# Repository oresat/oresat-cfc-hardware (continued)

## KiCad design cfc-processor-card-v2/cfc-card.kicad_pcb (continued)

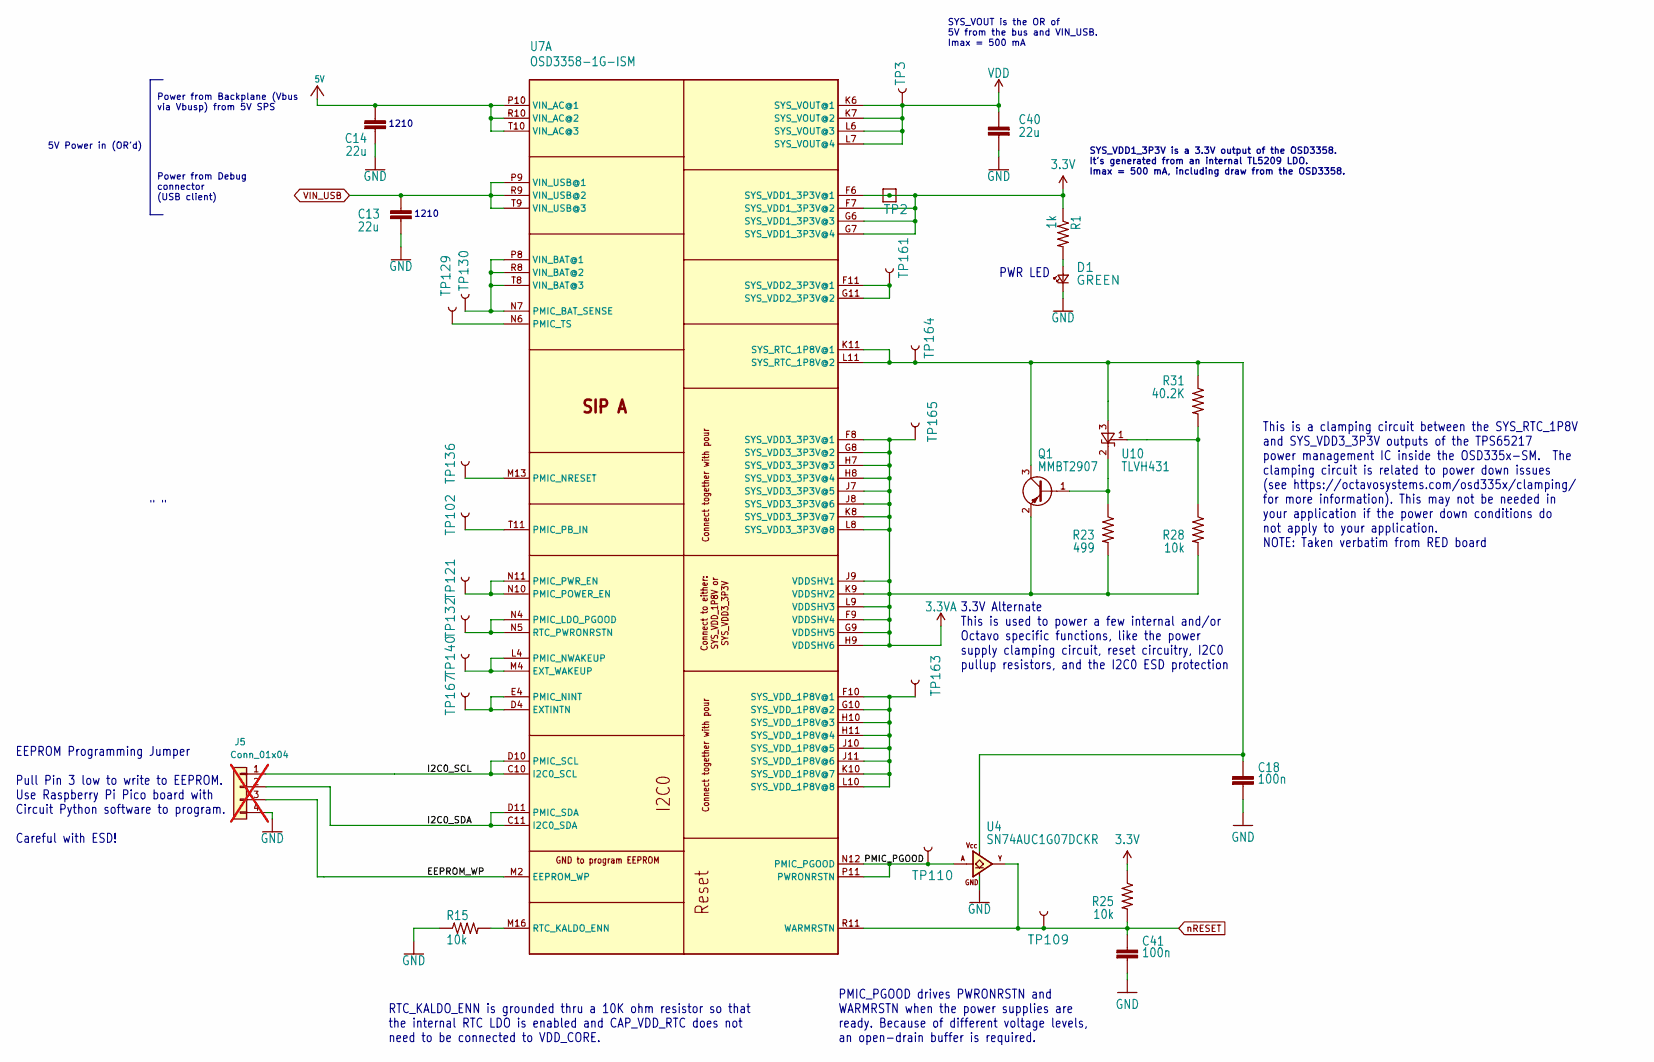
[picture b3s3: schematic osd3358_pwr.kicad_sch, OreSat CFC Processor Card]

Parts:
C13, C14, C40: 22u; C_1210_3225Metric; MPN GCM32EC71E226KE36K
C18, C41: 100n; 0603-C-NOSILK; MPN TMK107BJ104KAHT
D1: GREEN; LED_0603_1608Metric; MPN 150060GS75000
J5: Conn_01x04; PinHeader_1x04_P2.54mm_Vertical; not fitted
Q1: MMBT2907; SOT-23; MPN PMBT2907A,235
R1: 1k; 0603-C-NOSILK; MPN RMCF0603FT1K00
R15, R25, R28: 10k; 0603-C-NOSILK; MPN RMCF0603FT10K0
R23: 499; 0603-C-NOSILK; MPN RMCF0603FT499R
R31: 40.2K; 0603-C-NOSILK; MPN RMCF0603FT40K2
TP2: TEST-POINT; 2MM-TEST-POINT
TP3, TP102, TP109, TP110, TP121, TP129, TP130, TP132, TP136, TP140, TP161, TP163, TP164, TP165, TP167: TEST-POINT3X4; PAD.03X.04
U4: SN74AUC1G07DCKR; SOT-353_SC-70-5; MPN SN74AUC1G07DCKR
U7: OSD3358-1G-ISM; U-Octavo-OSD335X-BGA-256; MPN OSD3358-1G-ISM
U10: TLVH431; SOT-23; MPN TLVH431BCDBZT

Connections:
3.3V: R1.1, R25.1, TP2.1, U7.F6 (SYS_VDD1_3P3V@1), U7.F7 (SYS_VDD1_3P3V@2), U7.G6 (SYS_VDD1_3P3V@3), U7.G7 (SYS_VDD1_3P3V@4); also elsewhere on the board
3.3VA: Q1.2 (E), R23.2, R28.2, TP165.P$1 (1), U7.F8 (SYS_VDD3_3P3V@1), U7.F9 (VDDSHV4), U7.G8 (SYS_VDD3_3P3V@2), U7.G9 (VDDSHV5), U7.H7 (SYS_VDD3_3P3V@3), U7.H8 (SYS_VDD3_3P3V@4), U7.H9 (VDDSHV6), U7.J7 (SYS_VDD3_3P3V@5), U7.J8 (SYS_VDD3_3P3V@6), U7.J9 (VDDSHV1), U7.K8 (SYS_VDD3_3P3V@7), U7.K9 (VDDSHV2), U7.L8 (SYS_VDD3_3P3V@8), U7.L9 (VDDSHV3)
5V: C14.1, U7.P10 (VIN_AC@1), U7.R10 (VIN_AC@2), U7.T10 (VIN_AC@3); also elsewhere on the board
/OSD3358: SIP A (PWR)/EEPROM_WP: J5.3, U7.M2 (EEPROM_WP)
/OSD3358: SIP A (PWR)/I2C0_SCL: J5.1, U7.C10 (I2C0_SCL), U7.D10 (PMIC_SCL)
/OSD3358: SIP A (PWR)/I2C0_SDA: J5.2, U7.C11 (I2C0_SDA), U7.D11 (PMIC_SDA)
/OSD3358: SIP A (PWR)/PMIC_PGOOD: TP110.P$1 (1), U4.2 (A), U7.N12 (PMIC_PGOOD), U7.P11 (PWRONRSTN)
GND: C13.2, C14.2, C18.2, C40.2, C41.2, D1.1 (K), J5.4, R15.1, U4.3 (GND); also elsewhere on the board
unnamed: D1.2 (A), R1.2
unnamed: Q1.1 (B), R23.1, U10.2 (K)
unnamed: C18.1, Q1.3 (C), R31.1, TP164.P$1 (1), U4.5 (VCC), U7.K11 (SYS_RTC_1P8V@1), U7.L11 (SYS_RTC_1P8V@2), U10.3 (A)
unnamed: TP102.P$1 (1), U7.T11 (PMIC_PB_IN)
unnamed: TP121.P$1 (1), U7.N10 (PMIC_POWER_EN), U7.N11 (PMIC_PWR_EN)
unnamed: TP129.P$1 (1), U7.N6 (PMIC_TS)
unnamed: TP130.P$1 (1), U7.N7 (PMIC_BAT_SENSE), U7.P8 (VIN_BAT@1), U7.R8 (VIN_BAT@2), U7.T8 (VIN_BAT@3)
unnamed: TP132.P$1 (1), U7.N4 (PMIC_LDO_PGOOD), U7.N5 (RTC_PWRONRSTN)
unnamed: TP136.P$1 (1), U7.M13 (PMIC_NRESET)
unnamed: TP140.P$1 (1), U7.L4 (PMIC_NWAKEUP), U7.M4 (EXT_WAKEUP)
unnamed: TP161.P$1 (1), U7.F11 (SYS_VDD2_3P3V@1), U7.G11 (SYS_VDD2_3P3V@2)
unnamed: TP163.P$1 (1), U7.F10 (SYS_VDD_1P8V@1), U7.G10 (SYS_VDD_1P8V@2), U7.H10 (SYS_VDD_1P8V@3), U7.H11 (SYS_VDD_1P8V@4), U7.J10 (SYS_VDD_1P8V@5), U7.J11 (SYS_VDD_1P8V@6), U7.K10 (SYS_VDD_1P8V@7), U7.L10 (SYS_VDD_1P8V@8)
unnamed: TP167.P$1 (1), U7.D4 (EXTINTN), U7.E4 (PMIC_NINT)
unnamed: R15.2, U7.M16 (RTC_KALDO_ENN)
unnamed: R28.1, R31.2, U10.1 (REF)
VDD: C40.1, TP3.P$1 (1), U7.K6 (SYS_VOUT@1), U7.K7 (SYS_VOUT@2), U7.L6 (SYS_VOUT@3), U7.L7 (SYS_VOUT@4); also elsewhere on the board
VIN_USB: C13.1, U7.P9 (VIN_USB@1), U7.R9 (VIN_USB@2), U7.T9 (VIN_USB@3); also elsewhere on the board
nRESET: C41.1, R25.2, TP109.P$1 (1), U4.4 (Y), U7.R11 (WARMRSTN); also elsewhere on the board

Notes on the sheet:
SYS_VDD1_3P3V is a 3.3V output of the OSD3358. It's generated from an internal TL5209 LDO. Imax = 500 mA, including draw from the OSD3358.
PMIC_PGOOD drives PWRONRSTN and WARMRSTN when the power supplies are ready. Because of different voltage levels, an open-drain buffer is required.
" "
5V Power in (OR'd)
RTC_KALDO_ENN is grounded thru a 10K ohm resistor so that the internal RTC LDO is enabled and CAP_VDD_RTC does not need to be connected to VDD_CORE.
This is a clamping circuit between the SYS_RTC_1P8V and SYS_VDD3_3P3V outputs of the TPS65217 power management IC inside the OSD335x-SM. The clamping circuit is related to power down issues (see https://octavosystems.com/osd335x/clamping/ for more information). This may not be needed in your applic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
PWR LED
1210
EEPROM Programming Jumper Pull Pin 3 low to write to EEPROM. Use Raspberry Pi Pico board with Circuit Python software to program. Careful with ESD!
SYS_VOUT is the OR of 5V from the bus and VIN_USB. Imax = 500 mA
Power from Debug connector (USB client)
3.3V Alternate This is used to power a few internal and/or Octavo specific functions, like the power supply clamping circuit, reset circuitry, I2C0 pullup resistors, and the I2C0 ESD protection
Power from Backplane (Vbus via Vbusp) from 5V SPS

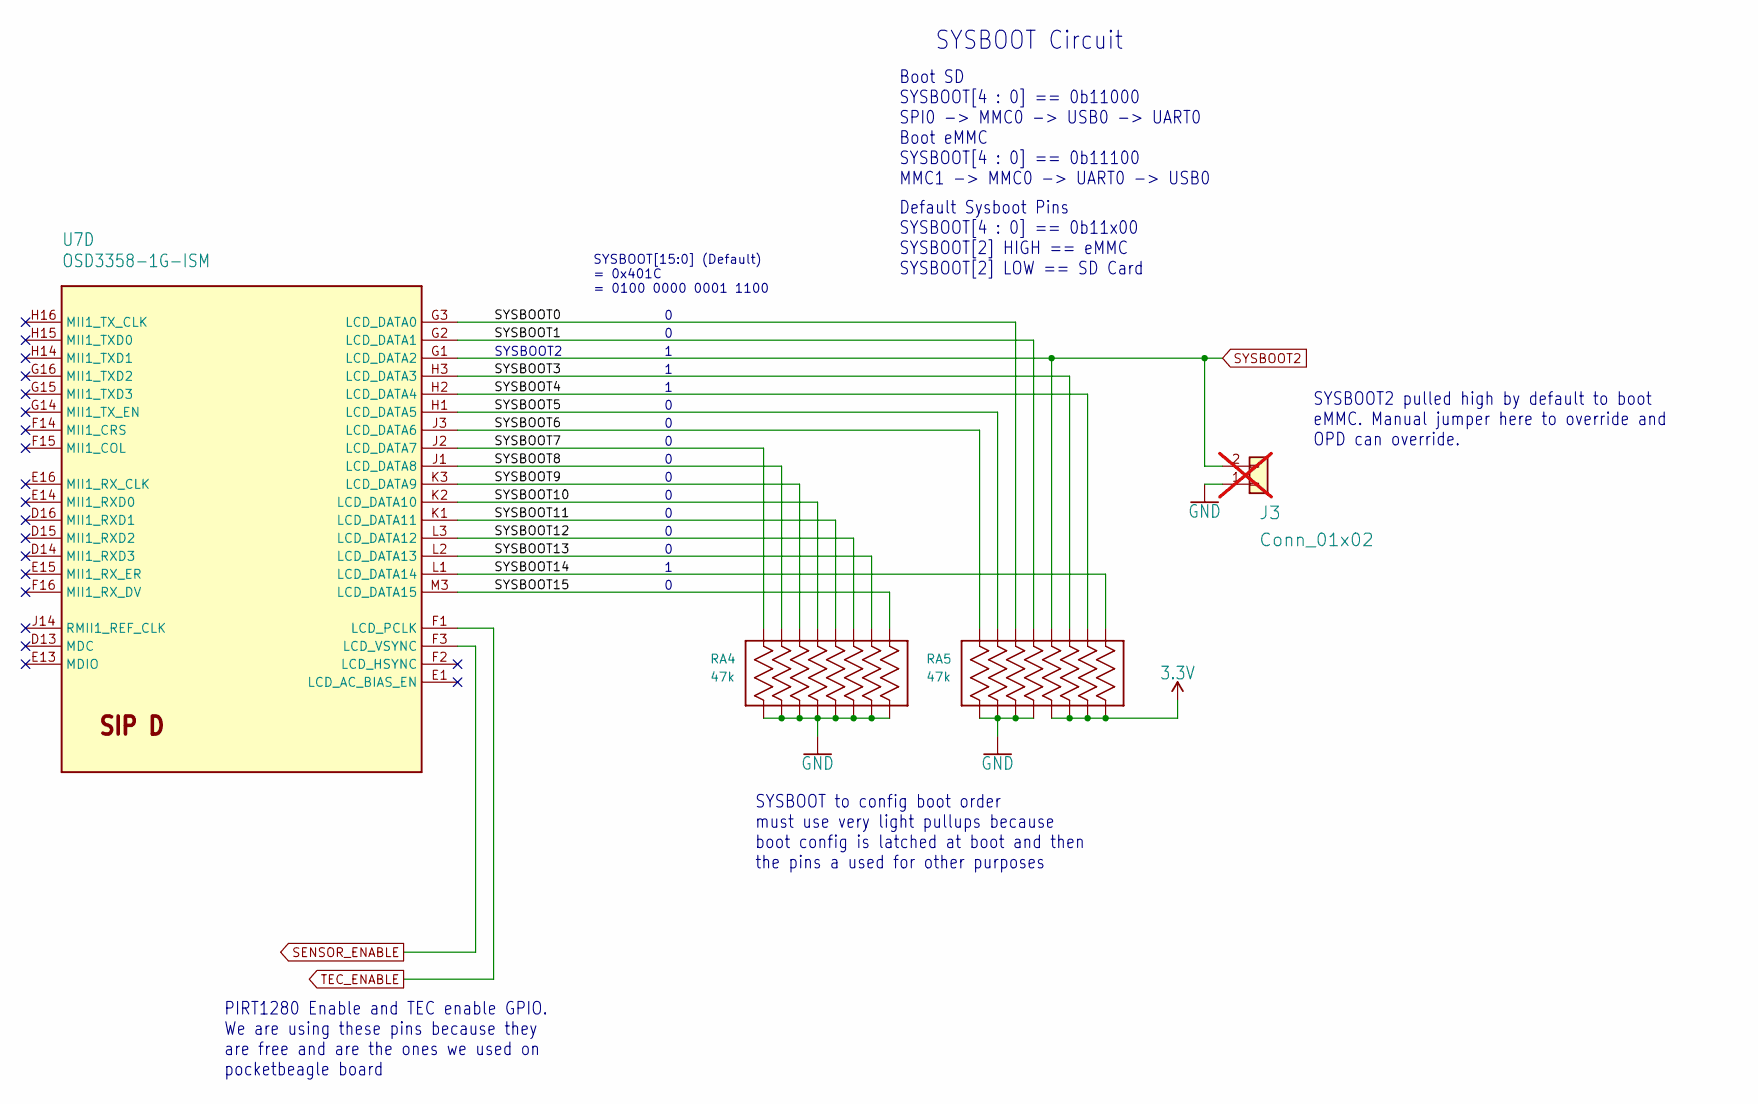
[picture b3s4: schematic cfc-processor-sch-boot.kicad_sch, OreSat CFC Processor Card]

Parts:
J3: Conn_01x02; PinHeader_1x02_P2.54mm_Vertical; not fitted
RA4, RA5: 47k; RES_EXB2HV; MPN EXB-2HV473JV
U7: OSD3358-1G-ISM; U-Octavo-OSD335X-BGA-256; MPN OSD3358-1G-ISM

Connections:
3.3V: RA5.5, RA5.6, RA5.7, RA5.8; also elsewhere on the board
/OSD3358: SIP D (BOOT)/SYSBOOT0: RA5.14, U7.G3 (LCD_DATA0)
/OSD3358: SIP D (BOOT)/SYSBOOT1: RA5.13, U7.G2 (LCD_DATA1)
/OSD3358: SIP D (BOOT)/SYSBOOT3: RA5.11, U7.H3 (LCD_DATA3)
/OSD3358: SIP D (BOOT)/SYSBOOT4: RA5.10, U7.H2 (LCD_DATA4)
/OSD3358: SIP D (BOOT)/SYSBOOT5: RA5.15, U7.H1 (LCD_DATA5)
/OSD3358: SIP D (BOOT)/SYSBOOT6: RA5.16, U7.J3 (LCD_DATA6)
/OSD3358: SIP D (BOOT)/SYSBOOT7: RA4.16, U7.J2 (LCD_DATA7)
/OSD3358: SIP D (BOOT)/SYSBOOT8: RA4.15, U7.J1 (LCD_DATA8)
/OSD3358: SIP D (BOOT)/SYSBOOT9: RA4.14, U7.K3 (LCD_DATA9)
/OSD3358: SIP D (BOOT)/SYSBOOT10: RA4.13, U7.K2 (LCD_DATA10)
/OSD3358: SIP D (BOOT)/SYSBOOT11: RA4.12, U7.K1 (LCD_DATA11)
/OSD3358: SIP D (BOOT)/SYSBOOT12: RA4.11, U7.L3 (LCD_DATA12)
/OSD3358: SIP D (BOOT)/SYSBOOT13: RA4.10, U7.L2 (LCD_DATA13)
/OSD3358: SIP D (BOOT)/SYSBOOT14: RA5.9, U7.L1 (LCD_DATA14)
/OSD3358: SIP D (BOOT)/SYSBOOT15: RA4.9, U7.M3 (LCD_DATA15)
GND: J3.1, RA4.1, RA4.2, RA4.3, RA4.4, RA4.5, RA4.6, RA4.7, RA4.8, RA5.1, RA5.2, RA5.3, RA5.4; also elsewhere on the board
SENSOR_ENABLE: U7.F3 (LCD_VSYNC); also elsewhere on the board
SYSBOOT2: J3.2, RA5.12, U7.G1 (LCD_DATA2); also elsewhere on the board
TEC_ENABLE: U7.F1 (LCD_PCLK); also elsewhere on the board

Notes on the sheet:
PIRT1280 Enable and TEC enable GPIO. We are using these pins because they are free and are the ones we used on pocketbeagle board
SYSBOOT Circuit
SYSBOOT[15:0] (Default) = 0x401C = 0100 0000 0001 1100
Boot SD SYSBOOT[4 : 0] == 0b11000 SPI0 -> MMC0 -> USB0 -> UART0 Boot eMMC SYSBOOT[4 : 0] == 0b11100 MMC1 -> MMC0 -> UART0 -> USB0
Default Sysboot Pins SYSBOOT[4 : 0] == 0b11x00 SYSBOOT[2] HIGH == eMMC SYSBOOT[2] LOW == SD Card
SYSBOOT to config boot order must use very light pullups because boot config is latched at boot and then the pins a used for other purposes
SYSBOOT2 pulled high by default to boot eMMC. Manual jumper here to override and OPD can override.
SYSBOOT2

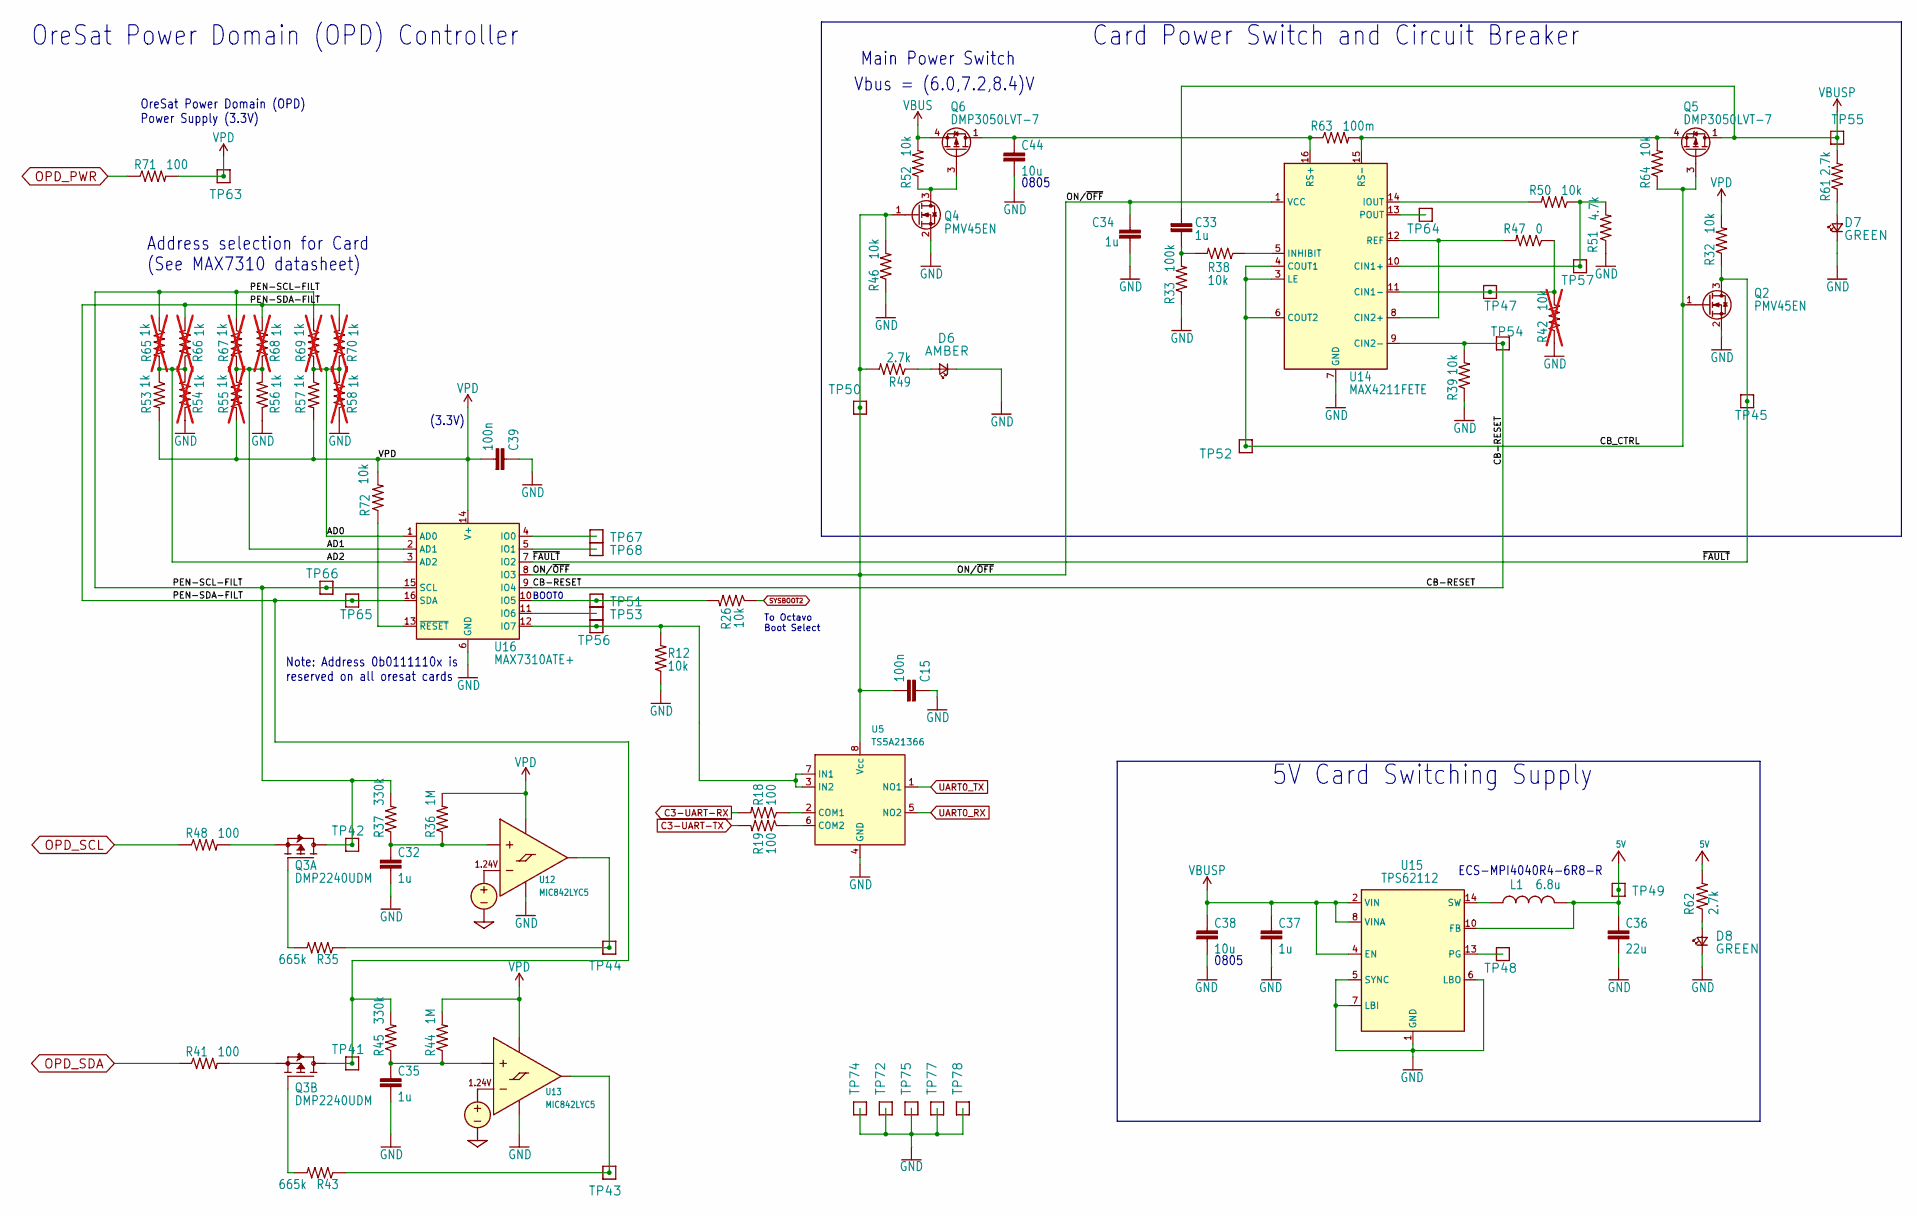
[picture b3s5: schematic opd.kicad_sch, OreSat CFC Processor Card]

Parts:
C15, C39: 100n; 0603-C-NOSILK; MPN TMK107BJ104KAHT
C32, C33, C34, C35, C37: 1u; 0603-C-NOSILK; MPN TMK107BJ105KAHT
C36: 22u; C_1210_3225Metric; MPN GCM32EC71E226KE36K
C38, C44: 10u; 0805-C-NOSILK; MPN GRT21BC71E106KE13L
D6: AMBER; LED_0603_1608Metric; MPN 150060AS75000
D7, D8: GREEN; LED_0603_1608Metric; MPN 150060GS75000
L1: 6.8u; L_ECS-MPI4040; MPN ECS-MPI4040R4-6R8-R
Q2, Q4: PMV45EN; SOT-23-3; MPN PMV45EN2R
Q3: DMP2240UDM; SOT-23-6; MPN DMP2240UDM
Q5, Q6: DMP3050LVT-7; TSOT-23-6; MPN DMP3050LVT-7
R12, R26, R32, R38, R39, R46, R50, R52, R64, R72: 10k; 0603-C-NOSILK; MPN RMCF0603FT10K0
R18, R19, R41, R48, R71: 100; 0603-C-NOSILK; MPN RMCF0603FT100R
R33: 100k; 0603-C-NOSILK; MPN RMCF0603FT100K
R35, R43: 665k; 0603-C-NOSILK; MPN RMCF0603FT665K
R36, R44: 1M; 0603-C-NOSILK; MPN RMCF0603FG1M00
R37, R45: 330k; 0603-C-NOSILK; MPN RMCF0603FT330K
R42: 10k; 0603-C-NOSILK; MPN RC1005F6653CS; not fitted
R47: 0; 0603-C-NOSILK; MPN RMCF0603ZT0R00
R49, R61, R62: 2.7k; 0603-C-NOSILK; MPN RMCF0603FT2K70
R51: 4.7k; 0603-C-NOSILK; MPN RMCF0603FT4K70
R53, R56, R57: 1k; 0603-C-NOSILK; MPN RMCF0603FT1K00
R54, R55, R58, R65, R66, R67, R68, R69, R70: 1k; 0603-C-NOSILK; MPN RC1005F6653CS; not fitted
R63: 100m; 1206-C; MPN CSR1206FTR100
TP41, TP42, TP43, TP44, TP45, TP47, TP48, TP49, TP50, TP51, TP52, TP53, TP54, TP55, TP56, TP57, TP63, TP64, TP65, TP66, TP67, TP68, TP72, TP74, TP75, TP77, TP78: TEST-POINT; 2MM-TEST-POINT
U5: TS5A21366; VSSOP-8_2.3x2mm_P0.5mm; MPN TS5A21366DCUR
U12, U13: MIC842LYC5; SOT-353_SC-70-5; MPN MIC842LYC5-TR
U14: MAX4211FETE; QFN-16-1EP_4x4mm_P0.65mm_EP2.1x2.1mm; MPN MAX4211FETE
U15: TPS62112; Texas_RSA_VQFN-16-1EP_4x4mm_P0.65mm_EP2.7x2.7mm; MPN TPS62112RSAR
U16: MAX7310ATE+; QFN-16-1EP_4x4mm_P0.65mm_EP2.1x2.1mm; MPN MAX7310ATE+

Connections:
5V: C36.1, L1.2, R62.2, TP49.1, U15.10 (FB); also elsewhere on the board
/Power (OPD)/AD0: R57.1, R58.2, R69.2, R70.1, U16.1 (AD0)
/Power (OPD)/AD1: R55.1, R56.2, R67.2, R68.1, U16.2 (AD1)
/Power (OPD)/AD2: R53.1, R54.2, R65.2, R66.1, U16.3 (AD2)
/Power (OPD)/CB-RESET: R39.2, TP54.1, U14.9 (CIN2-), U16.9 (IO4)
/Power (OPD)/CB_CTRL: Q2.1 (G), Q5.3 (G), R64.1, TP52.1, U14.3 (LE), U14.4 (COUT1), U14.6 (COUT2)
/Power (OPD)/ON/~OFF: C15.2, C34.1, Q4.1 (G), R46.2, R49.2, TP50.1, U5.8 (Vcc), U14.1 (VCC), U16.8 (IO3)
/Power (OPD)/PEN-SCL-FILT: Q3.6 (D), R37.2, R65.1, R67.1, R69.1, TP42.1, TP66.1, U16.15 (SCL)
/Power (OPD)/PEN-SDA-FILT: Q3.4 (D), R45.2, R66.2, R68.2, R70.2, TP41.1, TP65.1, U16.16 (SDA)
/Power (OPD)/~FAULT: Q2.3 (D), R32.1, TP45.1, U16.7 (IO2)
C3-UART-RX: R18.2; also elsewhere on the board
C3-UART-TX: R19.2; also elsewhere on the board
GND: C15.1, C32.2, C34.2, C35.2, C36.2, C37.2, C38.2, C39.1, C44.2, D6.1 (K), D7.1 (K), D8.1 (K), Q2.2 (S), Q4.2 (S), R12.1, R33.1, R39.1, R42.1, R46.1, R51.1, R54.1, R56.1, R58.1, TP72.1, TP74.1, TP75.1, TP77.1, TP78.1, U5.4 (GND), U12.2 (GND), U13.2 (GND), U14.7 (GND), U14.17 (GND), U15.1 (GND), U15.5 (SYNC), U15.6 (LBO), U15.7 (LBI), U15.9 (GND), U15.11 (GND), U15.12 (GND), U15.16 (GND), U15.17 (GND), U16.6 (GND), U16.17 (GND); also elsewhere on the board
unnamed: C33.1, R33.2, R38.2
unnamed: D6.2 (A), R49.1
unnamed: D7.2 (A), R61.1
unnamed: D8.2 (A), R62.1
unnamed: L1.1, U15.14 (SW), U15.15 (SW)
unnamed: Q3.1 (G), R35.2
unnamed: Q3.5 (S), R48.2
unnamed: Q3.3 (G), R43.2
unnamed: Q3.2 (S), R41.2
unnamed: Q4.3 (D), Q6.3 (G), R52.1
unnamed: Q5.4 (S), R63.2, R64.2, U14.15 (RS-)
unnamed: R18.1, U5.2 (COM1)
unnamed: R19.1, U5.6 (COM2)
unnamed: C32.1, R36.1, R37.1, U12.1 (INP)
unnamed: R35.1, TP44.1, U12.4 (OUT)
unnamed: C35.1, R44.1, R45.1, U13.1 (INP)
unnamed: R43.1, TP43.1, U13.4 (OUT)
unnamed: R50.1, R51.2, TP57.1, U14.10 (CIN1+)
unnamed: R42.2, R47.1, TP47.1, U14.11 (CIN1-)
unnamed: R47.2, U14.8 (CIN2+), U14.12 (REF)
unnamed: R38.1, U14.5 (INHIBIT)
unnamed: R50.2, U14.14 (IOUT)
unnamed: TP64.1, U14.13 (POUT)
unnamed: C44.1, Q6.1 (D), Q6.2 (D), Q6.5 (D), Q6.6 (D), R63.1, U14.16 (RS+)
unnamed: TP48.1, U15.13 (PG)
unnamed: TP67.1, U16.4 (IO0)
unnamed: TP68.1, U16.5 (IO1)
unnamed: R26.2, TP51.1, U16.10 (IO5)
unnamed: TP53.1, U16.11 (IO6)
unnamed: R12.2, TP56.1, U5.3 (IN2), U5.7 (IN1), U16.12 (IO7)
unnamed: R72.1, U16.13 (~RESET)
OPD_PWR: R71.1; also elsewhere on the board
OPD_SCL: R48.1; also elsewhere on the board
OPD_SDA: R41.1; also elsewhere on the board
SYSBOOT2: R26.1; also elsewhere on the board
UART0_RX: U5.5 (NO2); also elsewhere on the board
UART0_TX: U5.1 (NO1); also elsewhere on the board
VBUS: Q6.4 (S), R52.2; also elsewhere on the board
VBUSP: C33.2, C37.1, C38.1, Q5.1 (D), Q5.2 (D), Q5.5 (D), Q5.6 (D), R61.2, TP55.1, U15.2 (VIN), U15.3 (VIN), U15.4 (EN), U15.8 (VINA)
VPD: C39.2, R32.2, R36.2, R44.2, R53.2, R55.2, R57.2, R71.2, R72.2, TP63.1, U12.5 (VDD), U13.5 (VDD), U16.14 (V+)

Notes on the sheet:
0805
Card Power Switch and Circuit Breaker
BOOT0
Main Power Switch
OreSat Power Domain (OPD) Controller
ECS-MPI4040R4-6R8-R
(3.3V)
OreSat Power Domain (OPD) Power Supply (3.3V)
Address selection for Card (See MAX7310 datasheet)
To Octavo Boot Select
Vbus = (6.0,7.2,8.4)V
5V Card Switching Supply
Note: Address 0b0111110x is reserved on all oresat cards

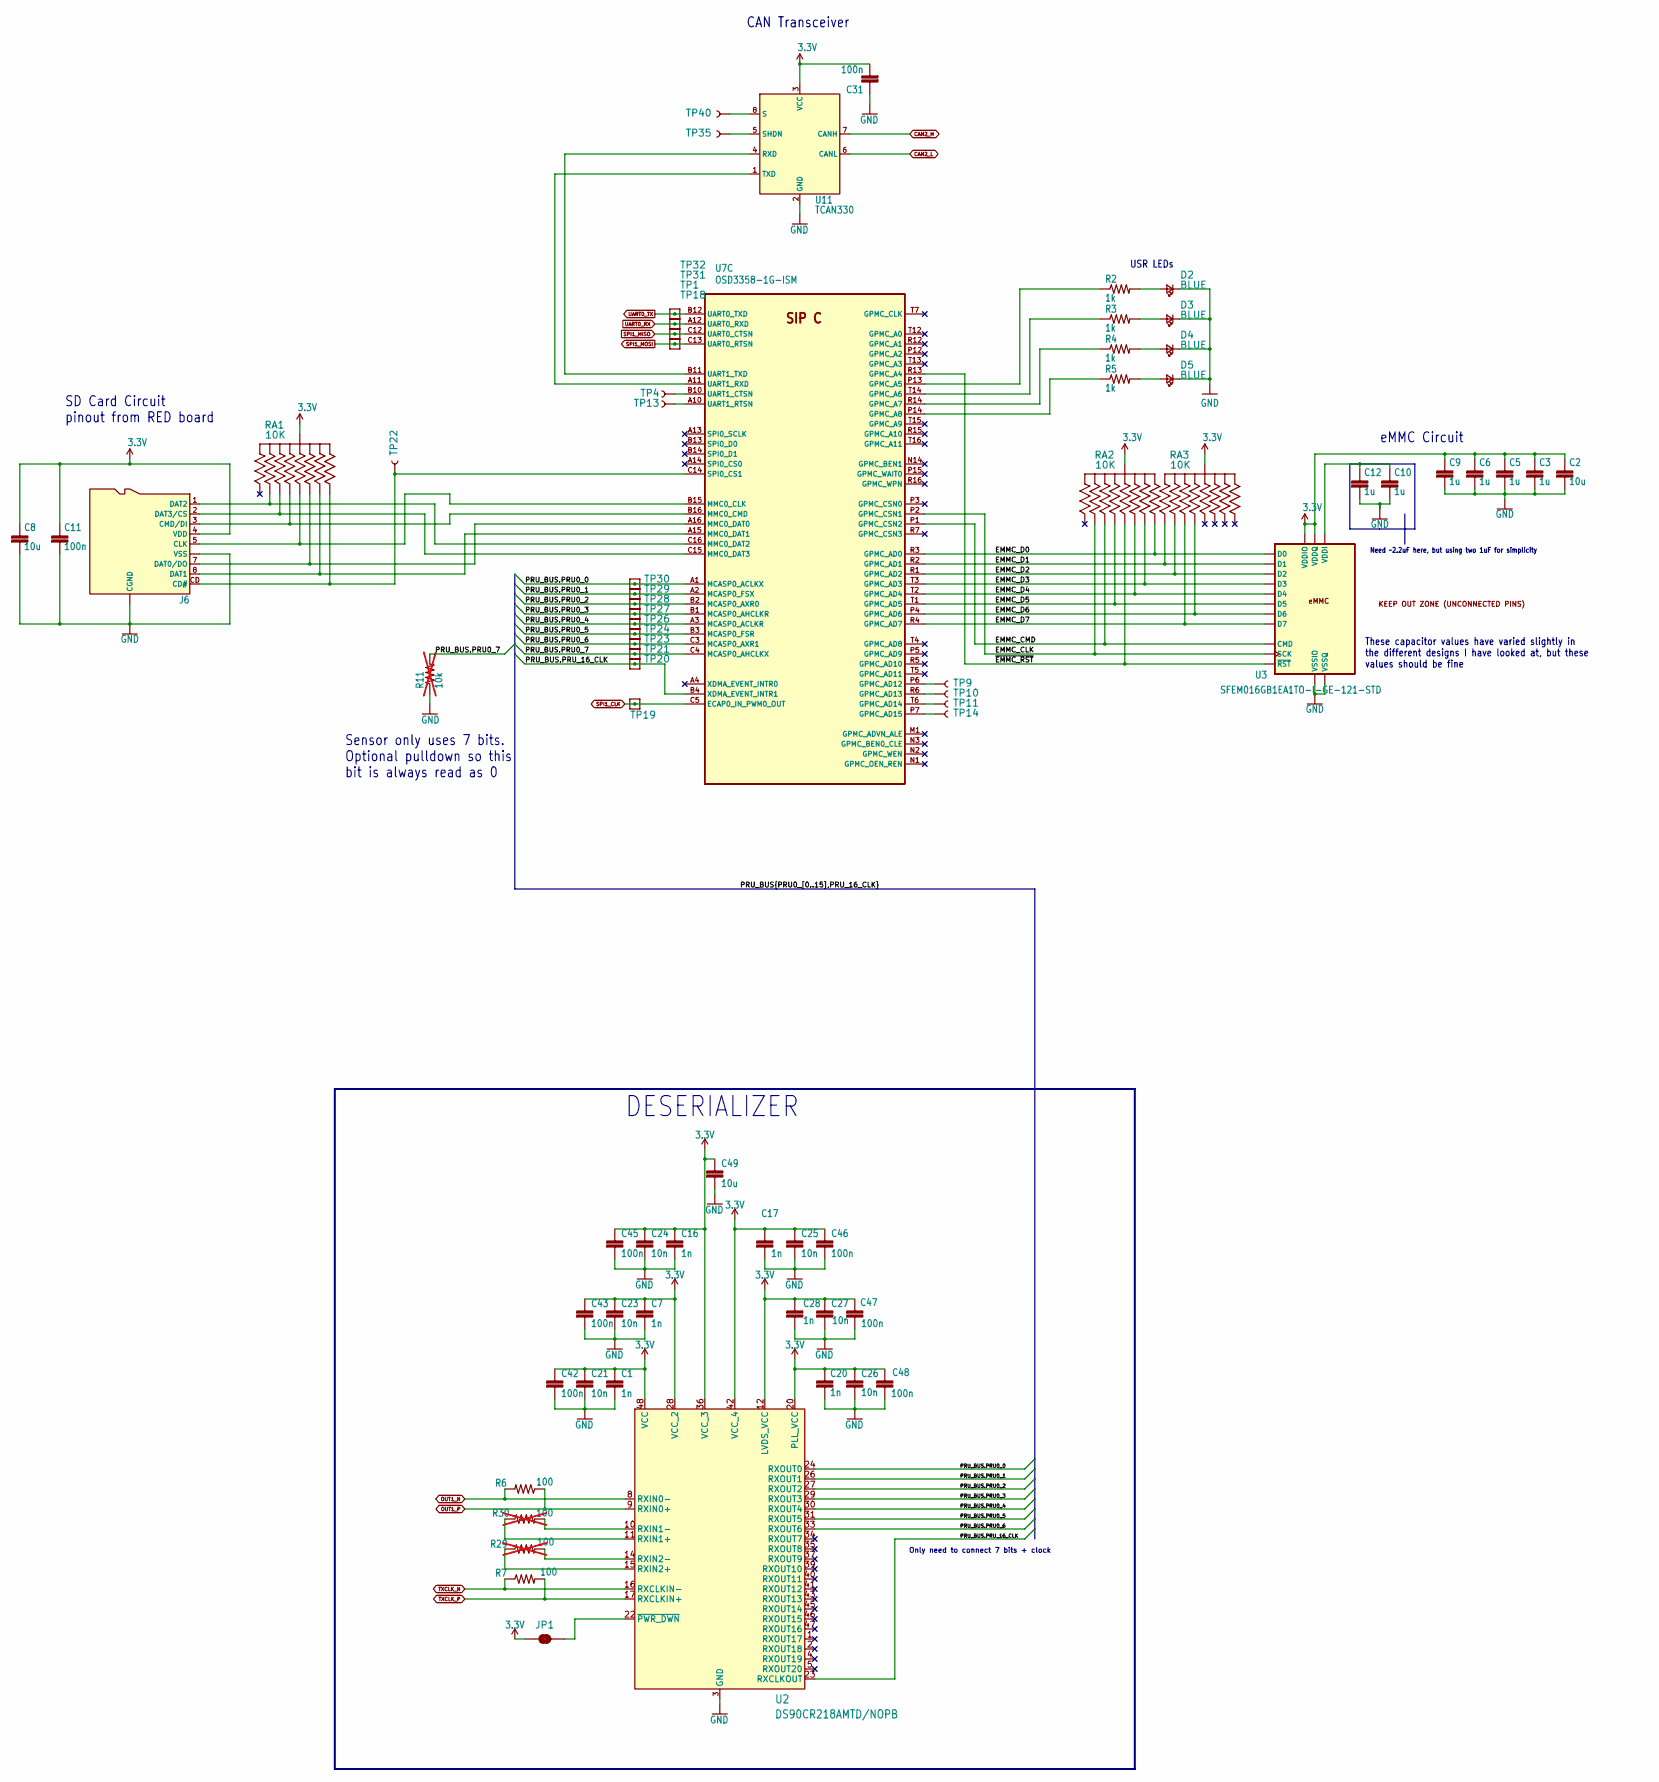
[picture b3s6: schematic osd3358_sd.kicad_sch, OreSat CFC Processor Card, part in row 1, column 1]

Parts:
C1, C7, C16, C17, C20, C28: 1n; 0402-C-NOSILK; MPN C0402C102J3GACAUTO
C2, C8, C49: 10u; 0805-C-NOSILK; MPN GRT21BC71E106KE13L
C3, C5, C6, C9, C10, C12: 1u; 0603-C-NOSILK; MPN TMK107BJ105KAHT
C11, C31: 100n; 0603-C-NOSILK; MPN TMK107BJ104KAHT
C21, C23, C24, C25, C26, C27: 10n; 0402-C-NOSILK; MPN C0402C100F5GACAUTO
C42, C43, C45, C46, C47, C48: 100n; 0402-C-NOSILK; MPN C0402C104K4RECAUTO
D2, D3, D4, D5: BLUE; LED_0603_1608Metric; MPN 150060BS75000
J6: DM3BT-DSF-PEJS; J-Hirose-DM3BT-DSF-PEJS; MPN DM3BT-DSF-PEJS
JP1: JUMPER-SMT_2_NC_TRACE_SILK; SMT-JUMPER_2_NC_TRACE_SILK
R2, R3, R4, R5: 1k; 0603-C-NOSILK; MPN RMCF0603FT1K00
R6, R7: 100; 0402-C-NOSILK; MPN RMCF0402FT100R
R11: 10k; 0603-C-NOSILK; not fitted
R29, R30: 100; 0402-C-NOSILK; MPN RC0201FR-07100RL; not fitted
RA1, RA2, RA3: 10K; ARRAY_EXBA-M; MPN EXB-A10P103J
TP1, TP18, TP19, TP20, TP21, TP23, TP24, TP26, TP27, TP28, TP29, TP30, TP31, TP32: TEST-POINT; 2MM-TEST-POINT
TP4, TP9, TP10, TP11, TP13, TP14, TP22, TP35, TP40: TEST-POINT3X4; PAD.03X.04
U2: DS90CR218AMTD/NOPB; MTD48_TEX-L; MPN DS90CR218AMTD/NOPB
U3: SFEM016GB1EA1TO-I-GE-121-STD; BGA-153(11.5X13)(EMMC-BA); MPN SFEM016GB1EA1TO-I-GE-121-STD
U7: OSD3358-1G-ISM; U-Octavo-OSD335X-BGA-256; MPN OSD3358-1G-ISM
U11: TCAN330; SOT-23-8; MPN TCAN330GDCNT

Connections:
3.3V: C1.1, C2.1, C3.1, C5.1, C6.1, C7.1, C8.1, C9.1, C11.1, C16.1, C17.1, C20.1, C21.1, C23.1, C24.1, C25.1, C26.1, C27.1, C28.1, C31.2, C42.1, C43.1, C45.1, C46.1, C47.1, C48.1, C49.1, J6.4 (VDD), JP1.1, RA1.5 (55), RA1.10 (55), RA2.5 (55), RA2.10 (55), RA3.5 (55), RA3.10 (55), U2.12 (LVDS_VCC), U2.20 (PLL_VCC), U2.28 (VCC_2), U2.36 (VCC_3), U2.42 (VCC_4), U2.48 (VCC), U3.C6 (VDDQ), U3.E6 (VDDIO), U3.F5 (VDDIO), U3.J10 (VDDIO), U3.K9 (VDDIO), U3.M4 (VDDQ), U3.N4 (VDDQ), U3.P3 (VDDQ), U3.P5 (VDDQ), U11.3 (VCC); also elsewhere on the board
/OSD3358: SIP C (SD, eMMC, PRU)/EMMC_CLK: RA2.9 (99), U3.M6 (SCK), U7.P2 (GPMC_CSN1)
/OSD3358: SIP C (SD, eMMC, PRU)/EMMC_CMD: RA2.2 (22), U3.M5 (CMD), U7.P1 (GPMC_CSN2)
/OSD3358: SIP C (SD, eMMC, PRU)/EMMC_D0: RA2.6 (66), U3.A3 (D0), U7.R3 (GPMC_AD0)
/OSD3358: SIP C (SD, eMMC, PRU)/EMMC_D1: RA3.1 (11), U3.A4 (D1), U7.R2 (GPMC_AD1)
/OSD3358: SIP C (SD, eMMC, PRU)/EMMC_D2: RA3.9 (99), U3.A5 (D2), U7.R1 (GPMC_AD2)
/OSD3358: SIP C (SD, eMMC, PRU)/EMMC_D3: RA2.4 (44), U3.B2 (D3), U7.T3 (GPMC_AD3)
/OSD3358: SIP C (SD, eMMC, PRU)/EMMC_D4: RA2.7 (77), U3.B3 (D4), U7.T2 (GPMC_AD4)
/OSD3358: SIP C (SD, eMMC, PRU)/EMMC_D5: RA2.8 (88), U3.B4 (D5), U7.T1 (GPMC_AD5)
/OSD3358: SIP C (SD, eMMC, PRU)/EMMC_D6: RA3.8 (88), U3.B5 (D6), U7.P4 (GPMC_AD6)
/OSD3358: SIP C (SD, eMMC, PRU)/EMMC_D7: RA3.2 (22), U3.B6 (D7), U7.R4 (GPMC_AD7)
/OSD3358: SIP C (SD, eMMC, PRU)/PRU_BUS.PRU0_0: TP30.1, U2.24 (RXOUT0), U7.A1 (MCASP0_ACLKX)
/OSD3358: SIP C (SD, eMMC, PRU)/PRU_BUS.PRU0_1: TP29.1, U2.26 (RXOUT1), U7.A2 (MCASP0_FSX)
/OSD3358: SIP C (SD, eMMC, PRU)/PRU_BUS.PRU0_2: TP28.1, U2.27 (RXOUT2), U7.B2 (MCASP0_AXR0)
/OSD3358: SIP C (SD, eMMC, PRU)/PRU_BUS.PRU0_3: TP27.1, U2.29 (RXOUT3), U7.B1 (MCASP0_AHCLKR)
/OSD3358: SIP C (SD, eMMC, PRU)/PRU_BUS.PRU0_4: TP26.1, U2.30 (RXOUT4), U7.A3 (MCASP0_ACLKR)
/OSD3358: SIP C (SD, eMMC, PRU)/PRU_BUS.PRU0_5: TP24.1, U2.31 (RXOUT5), U7.B3 (MCASP0_FSR)
/OSD3358: SIP C (SD, eMMC, PRU)/PRU_BUS.PRU0_6: TP23.1, U2.33 (RXOUT6), U7.C3 (MCASP0_AXR1)
/OSD3358: SIP C (SD, eMMC, PRU)/PRU_BUS.PRU0_7: R11.2, TP21.1, U7.C4 (MCASP0_AHCLKX)
/OSD3358: SIP C (SD, eMMC, PRU)/PRU_BUS.PRU_16_CLK: TP20.1, U2.23 (RXCLKOUT), U7.B4 (XDMA_EVENT_INTR1)
/OSD3358: SIP C (SD, eMMC, PRU)/~EMMC_RST: RA2.3 (33), U3.K5 (~RST), U7.R13 (GPMC_A4)
CAN2_H: U11.7 (CANH); also elsewhere on the board
CAN2_L: U11.6 (CANL); also elsewhere on the board
GND: C1.2, C2.2, C3.2, C5.2, C6.2, C7.2, C8.2, C9.2, C10.2, C11.2, C12.2, C16.2, C17.2, C20.2, C21.2, C23.2, C24.2, C25.2, C26.2, C27.2, C28.2, C31.1, C42.2, C43.2, C45.2, C46.2, C47.2, C48.2, C49.2, D2.1 (K), D3.1 (K), D4.1 (K), D5.1 (K), J6.6 (VSS), J6.CGND1 (CGND), J6.CGND2 (CGND), J6.CGND3 (CGND), J6.CGND4 (CGND), J6.CGND5 (CGND), J6.CGND6 (CGND), J6.GND (VSS), R11.1, U2.3 (GND), U2.7 (GND), U2.13 (GND), U2.18 (GND), U2.19 (GND), U2.21 (GND), U2.25 (GND), U2.32 (GND), U2.38 (GND), U2.44 (GND), U3.A6 (VSSIO), U3.C4 (VSSQ), U3.E7 (VSSIO), U3.G5 (VSSIO), U3.H10 (VSSIO), U3.J5 (VSSIO), U3.K8 (VSSIO), U3.N2 (VSSQ), U3.N5 (VSSQ), U3.P4 (VSSQ), U3.P6 (VSSQ), U11.2 (GND); also elsewhere on the board
unnamed: D2.2 (A), R2.2
unnamed: D3.2 (A), R3.2
unnamed: D4.2 (A), R4.2
unnamed: D5.2 (A), R5.2
unnamed: J6.CD (CD#), RA1.6 (66), TP22.P$1 (1), U7.C14 (SPI0_CS1)
unnamed: J6.5 (CLK), RA1.3 (33), U7.B15 (MMC0_CLK)
unnamed: J6.3 (CMD/DI), RA1.8 (88), U7.B16 (MMC0_CMD)
unnamed: J6.7 (DAT0/DO), RA1.7 (77), U7.A16 (MMC0_DAT0)
unnamed: J6.8 (DAT1), RA1.4 (44), U7.A15 (MMC0_DAT1)
unnamed: J6.1 (DAT2), RA1.9 (99), U7.C16 (MMC0_DAT2)
unnamed: J6.2 (DAT3/CS), RA1.2 (22), U7.C15 (MMC0_DAT3)
unnamed: TP4.P$1 (1), U7.B10 (UART1_CTSN)
unnamed: TP9.P$1 (1), U7.P6 (GPMC_AD12)
unnamed: TP10.P$1 (1), U7.R6 (GPMC_AD13)
unnamed: TP11.P$1 (1), U7.T6 (GPMC_AD14)
unnamed: TP13.P$1 (1), U7.A10 (UART1_RTSN)
unnamed: TP14.P$1 (1), U7.P7 (GPMC_AD15)
unnamed: TP35.P$1 (1), U11.5 (SHDN)
unnamed: TP40.P$1 (1), U11.8 (S)
unnamed: R30.1, U2.11 (RXIN1+)
unnamed: R30.2, U2.10 (RXIN1-)
unnamed: R29.1, U2.15 (RXIN2+)
unnamed: R29.2, U2.14 (RXIN2-)
unnamed: JP1.2, U2.22 (~PWR_DWN)
unnamed: C10.1, C12.1, U3.C2 (VDDI)
unnamed: R2.1, U7.P13 (GPMC_A5)
unnamed: R3.1, U7.T14 (GPMC_A6)
unnamed: R4.1, U7.R14 (GPMC_A7)
unnamed: R5.1, U7.P14 (GPMC_A8)
unnamed: U7.B11 (UART1_TXD), U11.4 (RXD)
unnamed: U7.A11 (UART1_RXD), U11.1 (TXD)
OUT1_N: R6.2, U2.8 (RXIN0-); also elsewhere on the board
OUT1_P: R6.1, U2.9 (RXIN0+); also elsewhere on the board
SPI1_CLK: TP19.1, U7.C5 (ECAP0_IN_PWM0_OUT); also elsewhere on the board
SPI1_MISO: TP1.1, U7.C12 (UART0_CTSN); also elsewhere on the board
SPI1_MOSI: TP18.1, U7.C13 (UART0_RTSN); also elsewhere on the board
TXCLK_N: R7.1, U2.16 (RXCLKIN-); also elsewhere on the board
TXCLK_P: R7.2, U2.17 (RXCLKIN+); also elsewhere on the board
UART0_RX: TP31.1, U7.A12 (UART0_RXD); also elsewhere on the board
UART0_TX: TP32.1, U7.B12 (UART0_TXD); also elsewhere on the board

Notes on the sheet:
USR LEDs
Sensor only uses 7 bits. Optional pulldown so this bit is always read as 0
DESERIALIZER
Need ~2.2uF here, but using two 1uF for simplicity
SD Card Circuit pinout from RED board
1.2
These capacitor values have varied slightly in the different designs I have looked at, but these values should be fine
CAN Transceiver
eMMC Circuit
Only need to connect 7 bits + clock

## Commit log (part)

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2020-07-16 first go around on the channel link test board
2020-07-17 minor cleanup, ground stitching, attributes
2020-07-19 moved LVDS lines so I could bypass the LVDS VCC
2020-07-20 ocd fixes
2020-07-20 Some minor DRCs.
2020-07-20 ROUND corners are BEST CORNERS.
2020-07-22 updated attributes and BOM
2021-01-18 Library file for the PIRT1280A1-12 camera.
2021-01-18 First pass at the PIRT breakout board.
2021-01-21 Mods from Oliver and Scott; more testpoints, stitching, ground points.
2021-01-26 Prototype of PIRT sensor and an example LT3042 power supply layout for one of the supplies.
2021-04-06 mostly finished PIRT breakout
2021-04-12 mostly finished with PIRT1280 carrier
2021-04-12 touch ups
2021-04-12 pre-review cleanup
2021-04-13 address review comments
2021-05-10 added PIRT1280 BOM, used internal library in carrier, added attributes
2021-05-10 Fixed BOM (a lot of wrong packages, no mfr, no descriptions, wrong formatting). Fixed 16 MHz crystal attributes.
2021-07-15 started cFC card
2021-07-20 rebase: backup work
2021-07-22 Add initial design for cfc emulator card
2021-07-22 Fix up ERC warnings
2021-07-23 Tweak up diff pairs and remove gerbers
2021-07-28 mostly finished sensor card
2021-08-01 mostly finished octavo card
2021-08-01 oh god almost done
2021-08-01 couple more changes
2021-08-01 remove todo
2021-08-02 boards finished
2021-08-02 update attrs
2021-08-02 xml change
2021-08-02 fixed resistor array value
2021-08-18 Fixed R27 attributes, and fixed names layer
2021-08-18 Added CFC sensor card BOM
2021-08-20 update attributes
2021-08-20 Updated OPD address resistors, LED resistors (AAAAAUGH MY EYES), and OPD shunt resistor to give the CFC sensor card addrss 0x1E and a 2.95 A current limit.
2021-08-24 Fix ~powerdown handling to add GPIO control from Icebreaker. Add pullup on ~powerdown to default it to powered up. Fix footprint error on TX chip (two pins swapped). Fix pin swap error on both LVDS p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
2022-11-08 Revamp the CFC hardware repo to keep v1 (giant copper block version) and start v2 (radiator version).
2022-11-08 OCD renaming
2022-11-08 New KiCAD project, schematic, and PCB layout for v2 of the CFC Sensor Board. Note that the schematic is empty, but the board reflects the 2022-09-15 sensor card outline from OnShape.
2022-11-08 Adding PIRT sensor. Needs a double check, and the rest of the symbol.
2022-11-09 Make sensor card thermal strap fastener passthroughts 5 mm so we can use a 4.5 mm washer.
2022-11-22 Add new DXF with bottom layer keepouts from the lens mount, and add it to the user.documentation layer.
2023-01-21 feat: cfc sensor card v2
2023-01-25 Changes from board fab: fixed card outline center hole (no fill), excluded some new violations, changed minimum mask web to 0.
2023-02-13 Generated ibom
2023-02-20 added OPD address resistors
2023-02-20 OPD CB shunt resistor is 10m, not 100m. Cleanup documentation. Also clean up documentation on other pages.
2023-05-12 Added CFC minibackplane requirements and drawing.
2023-05-13 Added note to Ben about a Ben Idea.
2023-05-14 Created a first revision of the mini backplane
2023-05-14 Updated 3d models
2023-05-14 Cleaned up schematic and silkscreen
2023-05-14 Switched to 2 layers
2023-05-14 Fixed silkscreen
2023-05-18 Updated outline DXF
2023-05-21 Updated board based on CFC meeting
2023-05-28 Made screws bigger and moved stuff
2023-05-28 Updated BOM
2023-06-01 Added formatted BOM for the minibackplane, including board connectors.
2023-06-19 Added not on Trinket wiring bug.
2023-07-16 Fixed wrong NPs in CFC sensor card OPD. Updated to KiCAD 7.
2023-07-26 Added TEC softstart LTspice simulation
2023-08-04 Added soft start to sensor card and cleaned up some KiCad warnings
2024-02-01 Add scripts subdirectory for test scripts for sensor. Add plothisto.py which plots histograms for the raw sensor pixel data
2025-06-12 Initial conversion of cfc processor board from Eagle to KiCAD 9
    Still using converted Eagle symbols and footprints.
2025-08-28 Clean up CFC Processor Card from Scott's initial import which was Gerber identical to origianl EAGLE schematic. Interestingly, this version was already changed for the v2 backplane which is great. Al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
2025-08-30 Big cleanup - fixed a billion ERCs and DRCs. Switched a bunch of parts over to OreSat parts. Added analog switch on UART so CFC processor can talk serial to C3. Last thing left: clean up passives wit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
2025-08-31 more trace polishing.
2025-08-31 More layout polishing Removed unused SPI EEPROM.
2025-09-13 Big sweep through to clean up from v2.0 to v2.1 board. Cleaned up all of the Github issues, and even added a MPS2410A CC driver to run the TEC for increased efficiency. Left old switch on board just 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
2025-09-13 renamed files to standard filenames, removed html file.
2025-09-13 Updated the README, finally
2025-09-13 Added a few pictures and cleaned up readme
2025-09-13 Links to pictures)
2025-09-13 adding license
2025-09-13 Final polish on README
2025-09-14 Final polish on schematic and PCB. Cleaned up BOM, fixed github issues which were not really issues. Lots of BOM cleanup, with MPNs and DPNs.
2025-09-14 Fix and complete BOM, fix lots of little layout issue and footprint inconsistancies, and polish. Ready to go!
2025-09-15 Changed mfg date, more stitching and layout tweaking.
2025-09-15 Updated mfg date. More stiching. More layout tweaking. Done.
2025-09-15 Rename old processor board since it's old and don't want people going there. Eventually, we'll remove, but those cards are still in use so worth it to have both for right now.
2025-09-15 Some minor cleanup on TEC schematic, no change to board
2025-09-15 File naming cleanup because OCD
2025-09-15 Final renaming!
2025-09-15 Fixed up crappy symbol on OPD; no change to layout, just schematic and link to PCB.
2026-06-23 Schematic Changes
    Made schematic into hierarchy view. Revised OPD to match modern OPD. Removed connectors page. Separated power sequencing and PIRT sensor into 2 pages.
2026-06-24 CFC processor schematic Change
    changed to hierarchy view, changed all global net labels to hierarchy labels, changed all resistor, capacitor, and ground symbols to modern oresat labels. Deleted connectors sheet and added .history 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
2026-06-24 Updated OPD
    couple of resistors and caps added to schematic. Changed USB ESD clamp VDD to 3.3v instead of octavo created VDD line.
2026-06-25 Update
    Added pull down resistors and removed therm + and sensor enable and added i2c support for cfc sensor card.
2026-06-27 Update
    Fixed a couple of library issues on testpoints and other misc components. Added Pull up resistors to 8 channel i2c ic
2026-06-28 Update
    Changed passive component footprints to 0603 no silk c. Fixed OPD UART termination resistor on cfc processor card. Added low temp co and tolerance resistor for NTC thermistor tec voltage divider.
2026-06-28 Update
    Cleaned up library preferences, added voltage controlled constant current note. Added RC filter to therm+ measurement made against the 2.5vref.
2026-06-30 Update
    Added bidirectional TEC control with DRV8212 IC. Added Sensor enable pin back to processor; in case of i2c hang up octavo can still disable sensor.
2026-06-30 update
    Changed a couple of test points on OPD to through hole test points. Added tables to DRV8212 on sensor schematic+ other visual improvements to processor schematic.
